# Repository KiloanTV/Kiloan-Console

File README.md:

<div>
  <h1 align="center">Kiloan Desk</h1>

  .png)

  <p align="center">
  <a href="https://blueprint.hackclub.com/">
    </img>
  </a>
  </p>
  <h1></h1>
  <p align="center">
    A customizable mixing console like high quality chassis system for building your own console systems.
  </p>
</div>

<sub align="center">This work is licensed under the
[MIT License](https://mit-license.org).
</sub>

## Table of Contents

- [About](#about)
- [Pictures](#pictures)
- [Bill of Materials](#bill-of-materials)

# About

I have a dream: a self-designed system where everyone can build the perfect mixing console/video console/DIY whatever console out of Aluminum Sheet Metal and a bit of the best hoppyist in house fabrication, 3d printing! And that's why I did this project, it's adapted somewhat to my current wishes and needs, but it can be individually adapted and replicated by anyone without breaking the budget.

# Pictures

# Bill of Materials

<details>
<summary><strong>Show Bill Of Materials(BOM) ----></strong></summary>

|Part Name                                                       |Quantity                                    |Price            |Vendor                                                 |Shipping Cost                                    |Total Cost       |Link(if applicable)                                                                                                                                                                                                                                                             |
|----------------------------------------------------------------|--------------------------------------------|-----------------|-------------------------------------------------------|-------------------------------------------------|-----------------|--------------------------------------------------------------------------------------------------------------------------------------------------------------------------------------------------------------------------------------------------------------------------------|
|Misc Front Module PCBs + Stencil                                |1x5                                         |€9.35            |jlcpcb                                                 |                                                 |                 |                                                                                                                                                                                                                                                                                |
|Fader Front Module PCBs + Stencil                               |1x5                                         |€16.58           |jlcpcb                                                 |                                                 |                 |                                                                                                                                                                                                                                                                                |
|Deck Switcher Front Module PCBs + Stencil                       |1x5                                         |€10.71           |jlcpcb                                                 |Shipping for all 3 PCB orders: €47.18            |                 |                                                                                                                                                                                                                                                                                |
|LCSC Electronic Components for 1x Deck Switcher/2x Fader/2x Misc|1 Order for everything(see lcsc cart export)|€87,81           |lcsc                                                   |€9,37                                            |                 |                                                                                                                                                                                                                                                                                |
|Keyswitches for the PCBs                                        |3x10pcs                                     |€5,20            |aliexpress                                             |€0                                               |                 |https://de.aliexpress.com/item/1005006814061416.html?spm=a2g0o.cart.0.0.639b4ae4hJRiNj&mp=1&pdp_npi=5%40dis%21EUR%21EUR%201.75%21EUR%201.75%21%21EUR%201.75%21%21%21%4021038da617652205559805350e63e4%2112000038390782462%21ct%21DE%216411673618%21%213%210&gatewayAdapt=glo2deu|
|M5x10mm Screws                                                  |3x100pcs                                    |€7,08            |schraubenking-shop.de(local and cheapest in my country)|                                                 |                 |https://www.schraubenking-shop.de/M5-x-10mm-Linsenkopfschrauben-TX-ISO14583-Edelstahl-A2-P004399                                                                                                                                                                                |
|M3x10mm Screws                                                  |1x100pcs                                    |€1,98            |schraubenking-shop.de(local and cheapest in my country)|Shipping for everything from schraubenking: €5,84|                 |https://www.schraubenking-shop.de/M3-x-10mm-Linsenkopfschrauben-TX-ISO14583-Edelstahl-A2-P004381                                                                                                                                                                                |
|JLCCNC Sheet Metal Parts                                        |10 individual parts                         |€146.97          |jlccnc                                                 |€78.28                                           |                 |jlccnc.com                                                                                                                                                                                                                                                                      |
|Estimated Total                                                 |                                            |€285,68 ($335,30)|                                                       |€140.67 ($165,15)                                |€426,35 ($500,56)|                                                                                                                                                                                                                                                                                |

</details>

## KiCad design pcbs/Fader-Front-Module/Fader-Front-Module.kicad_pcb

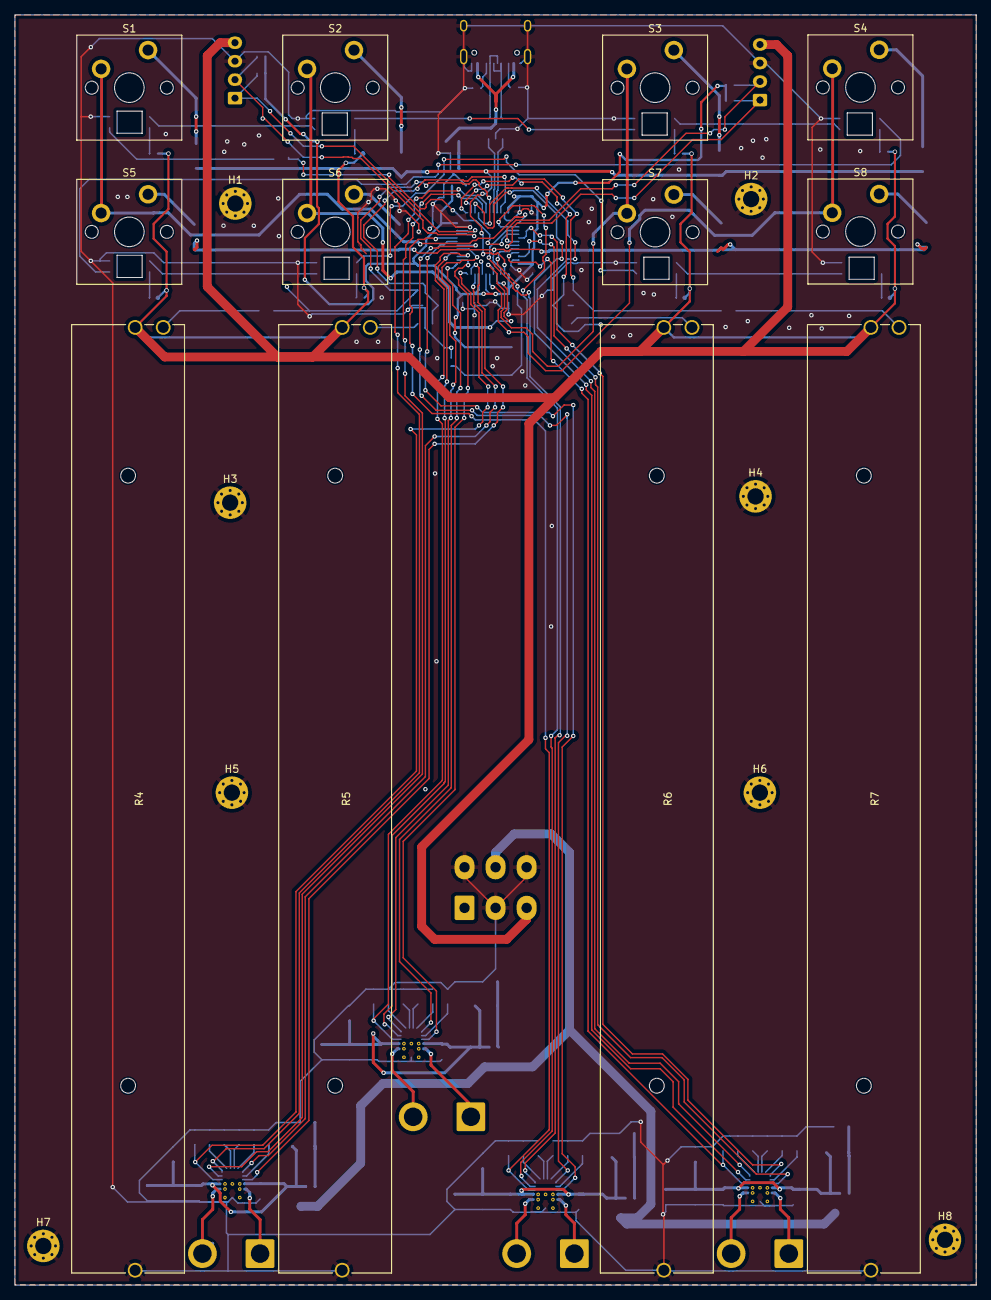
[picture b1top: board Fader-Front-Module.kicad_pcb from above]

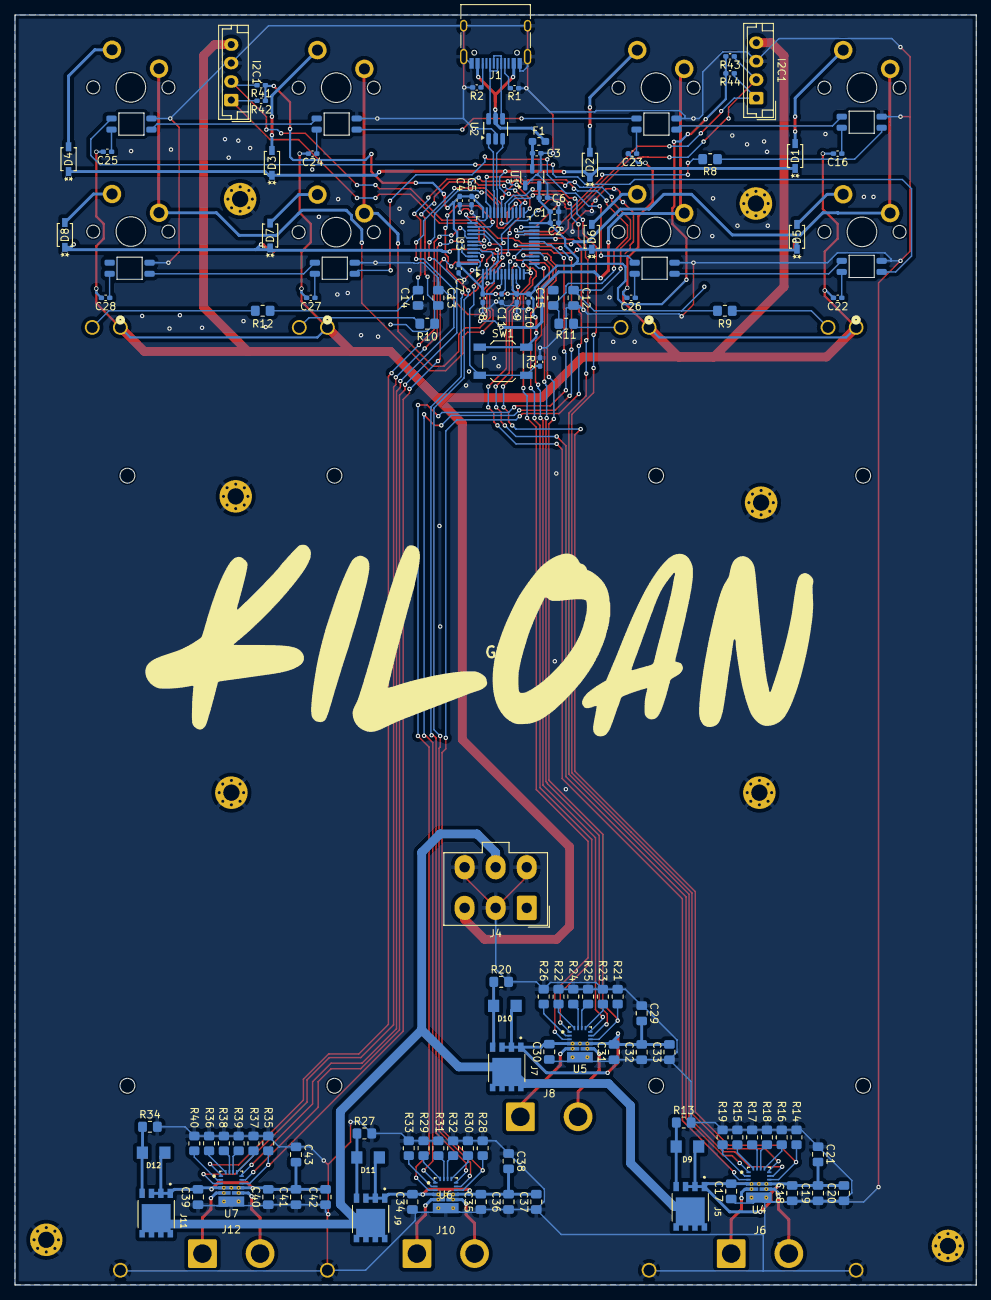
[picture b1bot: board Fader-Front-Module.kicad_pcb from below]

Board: 2 copper layers, 130.0 x 171.8 mm, 144 parts (124 on the bottom side), 113 nets.

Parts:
C1, C2, C5, C9, C11, C16, C22, C23, C24, C25, C26, C27, C28: 100nF; C_0402_1005Metric_Pad0.74x0.62mm_HandSolder
C3, C4, C8: 1uF; C_0402_1005Metric_Pad0.74x0.62mm_HandSolder
C6, C10: 4.7uF; C_0402_1005Metric_Pad0.74x0.62mm_HandSolder
C7: 10nF; C_0402_1005Metric_Pad0.74x0.62mm_HandSolder
C12, C13, C14, C15: 1nF; C_0805_2012Metric_Pad1.18x1.45mm_HandSolder
C17, C21, C29, C30, C34, C35, C39, C40: 10uF; C_0805_2012Metric_Pad1.18x1.45mm_HandSolder
C18, C31, C36, C41: 1uF; C_0805_2012Metric_Pad1.18x1.45mm_HandSolder
C19, C32, C37, C42: 100nF; C_0805_2012Metric_Pad1.18x1.45mm_HandSolder
C20, C33, C38, C43: 10nF; C_0805_2012Metric_Pad1.18x1.45mm_HandSolder
D1, D2, D3, D4, D5, D6, D7, D8: Diode; SOD-123_ONS
D9, D10, D11, D12: Motor Diode; LL-34
F1: 500mA; Fuse_0603_1608Metric_Pad1.05x0.95mm_HandSolder
H1, H2, H3, H4, H5, H6, H7, H8: MountingHole_Pad; MountingHole_2.2mm_M2_Pad_Via
J1: USB_C; USB_C_Receptacle_HRO_TYPE-C-31-M-12
J2, J3: I2C1; JST_EH_B4B-EH-A_1x04_P2.50mm_Vertical
J4: External PowerSupply; Molex_Mini-Fit_Jr_5566-06A_2x03_P4.20mm_Vertical
J5, J7, J9, J11: MOSFET P-CH 40V 70A PDFN5x6-8L; TRANS_TSM018NB03CR_RLG
J6, J8, J10, J12: motor_port_1; SolderWire-2sqmm_1x02_P7.8mm_D2mm_OD3.9mm
LED1, LED2, LED3, LED4, LED5, LED6, LED7, LED8: LED_SK6812MINI
R1, R2, R41, R42, R43, R44: 5.1k; C_0402_1005Metric_Pad0.74x0.62mm_HandSolder
R3: 10k; C_0402_1005Metric_Pad0.74x0.62mm_HandSolder
R4, R5, R6, R7: PTB0153-2010BPB103; schieberegler-PTB0153-2010BPB103
R8, R9, R10, R11, R12: 500Ω; R_0805_2012Metric_Pad1.20x1.40mm_HandSolder
R13, R18, R20, R25, R27, R32, R34, R39: 22kΩ; R_0805_2012Metric_Pad1.20x1.40mm_HandSolder
R14, R21, R28, R35: 1kΩ; R_0805_2012Metric_Pad1.20x1.40mm_HandSolder
R15, R16, R17, R19, R22, R23, R24, R26, R29, R30, R31, R33, R36, R37, R38, R40: 0Ω; R_0805_2012Metric_Pad1.20x1.40mm_HandSolder
S1, S2, S3, S4, S5, S6, S7, S8: Keyswitch; MX_PCB_1.00u
SW1: SW_Push; SW_SPST_TL3342
U1: XC6206; SOT-23-3
U2: USBLC6-2SC6; SOT-23-6_Handsoldering
U3: STM32F072CBT6; LQFP-48_7x7mm_P0.5mm
U4, U5, U6, U7: DRV8243HQRXYRQ1; RXY0014A-MFG

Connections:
+3.3V: C1.2, C2.2, C4.1, C5.2, C6.2, C7.2, C8.2, C9.2, C10.2, R41.2, R42.2, R43.2, R44.2, SW1.1, U1.2 (VO), U3.1 (VBAT), U3.9 (VDDA), U3.24 (VDD), U3.36 (VDDIO2), U3.48 (VDD)
+3.3VA: C16.2, C22.2, C23.2, C24.2, C25.2, C26.2, C27.2, C28.2, J2.4, J3.4, J4.3, R4.1, R5.1, R6.1, R7.1
+5V: C3.1, F1.1, U1.3 (VI)
+5VA: J4.5, J5.5_8 (Pin_9), J7.5_8 (Pin_8), J9.5_8 (Pin_5), J11.5_8 (Pin_9)
/BOOT: R3.2, SW1.2, U3.44 (BOOT0)
/MCU_D+: U2.1 (I/O1), U3.33 (PA12)
/MCU_D-: U2.3 (I/O2), U3.32 (PA11)
/NRST: C11.1, U3.7 (NRST)
/USB_D+: J1.A6 (D+), J1.B6 (D+), U2.6 (I/O1)
/USB_D-: J1.A7 (D-), J1.B7 (D-), U2.4 (I/O2)
Column 0: S1.1, S5.1, U3.37 (PA14)
Column 1: S2.1, S6.1, U3.4 (PC15)
Column 2: S3.1, S7.1, U3.5 (PF0)
Column 3: S4.1, S8.1, U3.6 (PF1)
DIAG_1: R16.1, U4.11 (SCS_N)
DIAG_2: R23.1, U5.11 (SCS_N)
DIAG_3: R30.1, U6.11 (SCS_N)
DIAG_4: R37.1, U7.11 (SCS_N)
DRVOFF_1: R14.1, U3.12 (PA2), U4.8 (DRVOFF)
DRVOFF_2: R21.1, U3.15 (PA5), U5.8 (DRVOFF)
DRVOFF_3: R28.1, U3.20 (PB2), U6.8 (DRVOFF)
DRVOFF_4: R35.1, U3.45 (PB8), U7.8 (DRVOFF)
EN/IN1_1: U3.29 (PA8), U4.9 (EN_IN1)
EN/IN1_2: U3.16 (PA6), U5.9 (EN_IN1)
EN/IN1_3: U3.38 (PA15), U6.9 (EN_IN1)
EN/IN1_4: U3.27 (PB14), U7.9 (EN_IN1)
EN/IN2_1: U3.30 (PA9), U4.10 (PH_IN2)
EN/IN2_2: U3.17 (PA7), U5.10 (PH_IN2)
EN/IN2_3: U3.39 (PB3), U6.10 (PH_IN2)
EN/IN2_4: U3.28 (PB15), U7.10 (PH_IN2)
Fader0: C12.2, R9.1, U3.31 (PA10)
Fader1: C15.2, R11.1, U3.34 (PA13)
Fader2: C13.2, R10.1, U3.25 (PB12)
Fader3: C14.2, R12.1, U3.26 (PB13)
GND: C1.1, C2.1, C3.2, C4.2, C5.1, C6.1, C7.1, C8.1, C9.1, C10.1, C11.2, C12.1, C13.1, C14.1, C15.1, C17.1, C18.1, C19.1, C20.1, C21.1, C29.1, C30.1, C31.1, C32.1, C33.1, C34.1, C35.1, C36.1, C37.1, C38.1, C39.1, C40.1, C41.1, C42.1, C43.1, H1.1, H2.1, H3.1, H4.1, H5.1, H6.1, H7.1, H8.1, J1.A1 (GND), J1.A12 (GND), J1.B1 (GND), J1.B12 (GND), J1.S1 (SHIELD), J2.3, J3.3, J4.2, J4.4, J4.6, LED1.3 (VSS), LED2.3 (VSS), LED3.3 (VSS), LED4.3 (VSS), LED5.3 (VSS), LED6.3 (VSS), LED7.3 (VSS), LED8.3 (VSS), R1.2, R2.2, R3.1, R4.3, R5.3, R6.3, R7.3, R13.2, R14.2, R15.2, R16.2, R17.2, R18.2, R19.2, R20.2, R21.2, R22.2, R23.2, R24.2, R25.2, R26.2, R27.2, R28.2, R29.2, R30.2, R31.2, R32.2, R33.2, R34.2, R35.2, R36.2, R37.2, R38.2, R39.2, R40.2, U1.1 (GND), U2.2 (GND), U3.8 (VSSA), U3.23 (VSS), U3.35 (VSS), U3.47 (VSS), U4.6 (GND), U5.6 (GND), U6.6 (GND), U7.6 (GND)
I2C1_SCL: J2.2, R41.1, U3.42 (PB6)
I2C1_SDA: J2.1, R42.1, U3.43 (PB7)
I2C2_SCL: J3.2, R43.1, U3.21 (PB10)
I2C2_SDA: J3.1, R44.1, U3.22 (PB11)
IPROPI_1: R19.1, U4.2 (IPROPI)
IPROPI_2: R26.1, U5.2 (IPROPI)
IPROPI_3: R33.1, U6.2 (IPROPI)
IPROPI_4: R40.1, U7.2 (IPROPI)
ITRIP_1: R17.1, U4.13 (SDI)
ITRIP_2: R24.1, U5.13 (SDI)
ITRIP_3: R31.1, U6.13 (SDI)
ITRIP_4: R38.1, U7.13 (SDI)
LED_DATA_IN: R8.2, U3.40 (PB4)
MODE_1: R15.1, U4.14 (SDO)
MODE_2: R22.1, U5.14 (SDO)
MODE_3: R29.1, U6.14 (SDO)
MODE_4: R36.1, U7.14 (SDO)
unnamed: D1.2 (A), S1.2
unnamed: D2.2 (A), S2.2
unnamed: D3.2 (A), S3.2
unnamed: D4.2 (A), S4.2
unnamed: D5.2 (A), S5.2
unnamed: D6.2 (A), S6.2
unnamed: D7.2 (A), S7.2
unnamed: D8.2 (A), S8.2
unnamed: D9.2 (A), J5.4, R13.1
unnamed: D10.2 (A), J7.4, R20.1
unnamed: D11.2 (A), J9.4, R27.1
unnamed: D12.2 (A), J11.4, R34.1
unnamed: J1.A5 (CC1), R1.1
unnamed: J1.B5 (CC2), R2.1
unnamed: LED1.2 (DIN), R8.1
unnamed: LED1.4 (DOUT), LED2.2 (DIN)
unnamed: C16.1, LED1.1 (VDD)
unnamed: LED2.4 (DOUT), LED3.2 (DIN)
unnamed: C23.1, LED2.1 (VDD)
unnamed: LED3.4 (DOUT), LED4.2 (DIN)
unnamed: C24.1, LED3.1 (VDD)
unnamed: LED4.4 (DOUT), LED5.2 (DIN)
unnamed: C25.1, LED4.1 (VDD)
unnamed: LED5.4 (DOUT), LED6.2 (DIN)
unnamed: C22.1, LED5.1 (VDD)
unnamed: LED6.4 (DOUT), LED7.2 (DIN)
unnamed: C26.1, LED6.1 (VDD)
unnamed: LED7.4 (DOUT), LED8.2 (DIN)
unnamed: C27.1, LED7.1 (VDD)
unnamed: C28.1, LED8.1 (VDD)
unnamed: R4.2, R9.2
unnamed: R6.2, R10.2
unnamed: R5.2, R11.2
unnamed: R7.2, R12.2
OUT1_1: J6.2, U4.7 (OUT1)
OUT1_2: J8.2, U5.7 (OUT1)
OUT1_3: J10.2, U6.7 (OUT1)
OUT1_4: J12.2, U7.7 (OUT1)
OUT2_1: J6.1, U4.5 (OUT2)
OUT2_2: J8.1, U5.5 (OUT2)
OUT2_3: J10.1, U6.5 (OUT2)
OUT2_4: J12.1, U7.5 (OUT2)
Row 0: D1.1 (K), D2.1 (K), D3.1 (K), D4.1 (K), U3.2 (PC13)
Row 1: D5.1 (K), D6.1 (K), D7.1 (K), D8.1 (K), U3.3 (PC14)
SR_1: R18.1, U4.12 (SCLK)
SR_2: R25.1, U5.12 (SCLK)
SR_3: R32.1, U6.12 (SCLK)
SR_4: R39.1, U7.12 (SCLK)
VBUS: F1.2, J1.A4 (VBUS), J1.A9 (VBUS), J1.B4 (VBUS), J1.B9 (VBUS), U2.5 (VBUS)
VSS_1: C17.2, C18.2, C19.2, C20.2, C21.2, D9.1 (K), J5.1, J5.2, J5.3, U4.4 (VM)
VSS_2: C29.2, C30.2, C31.2, C32.2, C33.2, D10.1 (K), J7.1, J7.2, J7.3, U5.4 (VM)
VSS_3: C34.2, C35.2, C36.2, C37.2, C38.2, D11.1 (K), J9.1, J9.2, J9.3, U6.4 (VM)
VSS_4: C39.2, C40.2, C41.2, C42.2, C43.2, D12.1 (K), J11.1, J11.2, J11.3, U7.4 (VM)
nFAULT_1: U3.10 (PA0), U4.1 (FAULT_N)
nFAULT_2: U3.13 (PA3), U5.1 (FAULT_N)
nFAULT_3: U3.18 (PB0), U6.1 (FAULT_N)
nFAULT_4: U3.41 (PB5), U7.1 (FAULT_N)
nSLEEP_1: U3.11 (PA1), U4.3 (SLEEP_N)
nSLEEP_2: U3.14 (PA4), U5.3 (SLEEP_N)
nSLEEP_3: U3.19 (PB1), U6.3 (SLEEP_N)
nSLEEP_4: U3.46 (PB9), U7.3 (SLEEP_N)

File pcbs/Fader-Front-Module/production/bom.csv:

Designator,Footprint,Quantity,Value,LCSC Part #
"C1, C11, C16, C2, C22, C23, C24, C25, C26, C27, C28, C5, C9",0402,13,100nF,C307331
"C10, C6",0402,2,4.7uF,C23733
"C12, C13, C14, C15",0805,4,1nF,C94121
"C17, C21, C29, C30, C34, C35, C39, C40",0805,8,10uF,C15850
"C18, C31, C36, C41",0805,4,1uF,C28323
"C19, C32, C37, C42",0805,4,100nF,C49678
"C20, C33, C38, C43",0805,4,10nF,C1710
"C3, C4, C8",0402,3,1uF,C52923
C7,0402,1,10nF,C15195
"D1, D2, D3, D4, D5, D6, D7, D8",SOD-123_ONS,8,Diode,C11177
"D10, D11, D12, D9",LL-34,4,Motor Diode,C2891753
F1,0603,1,500mA,C210357
J1,USB_C_Receptacle_HRO_TYPE-C-31-M-12,1,USB_C,C165948
"J10, J12, J6, J8",SolderWire-2sqmm_1x02_P7.8mm_D2mm_OD3.9mm,4,motor_port_1,
"J11, J5, J7, J9",TRANS_TSM018NB03CR_RLG,4,MOSFET P-CH 40V 70A PDFN5x6-8L,C5297498
"J2, J3",JST_EH_B4B-EH-A_1x04_P2.50mm_Vertical,2,I2C1,C160258
J4,Molex_Mini-Fit_Jr_5566-06A_2x03_P4.20mm_Vertical,1,External PowerSupply,C471417
"LED1, LED2, LED3, LED4, LED5, LED6, LED7, LED8",LED_SK6812MINI,8,LED_SK6812MINI,C5149201
"R1, R2, R41, R42, R43, R44",0402,6,5.1k,C25905
"R10, R11, R12, R8, R9",0805,5,500Ω,C2828857
"R13, R18, R20, R25, R27, R32, R34, R39",0805,8,22kΩ,C2907243
"R14, R21, R28, R35",0805,4,1kΩ,C95781
"R15, R16, R17, R19, R22, R23, R24, R26, R29, R30, R31, R33, R36, R37, R38, R40",0805,16,0Ω,DNP
R3,0402,1,10k,C25744
"R4, R5, R6, R7",schieberegler-PTB0153-2010BPB103,4,PTB0153-2010BPB103,C17427549
"S1, S2, S3, S4, S5, S6, S7, S8",MX_PCB_1.00u,8,Keyswitch,
SW1,SW_SPST_TL3342,1,SW_Push,C115351
U1,SOT-23-3,1,XC6206,C5446
U2,SOT-23-6_Handsoldering,1,USBLC6-2SC6,C2827654
U3,LQFP-48_7x7mm_P0.5mm,1,STM32F072CBT6,C81720
"U4, U5, U6, U7",RXY0014A-MFG,4,DRV8243HQRXYRQ1,C3040833

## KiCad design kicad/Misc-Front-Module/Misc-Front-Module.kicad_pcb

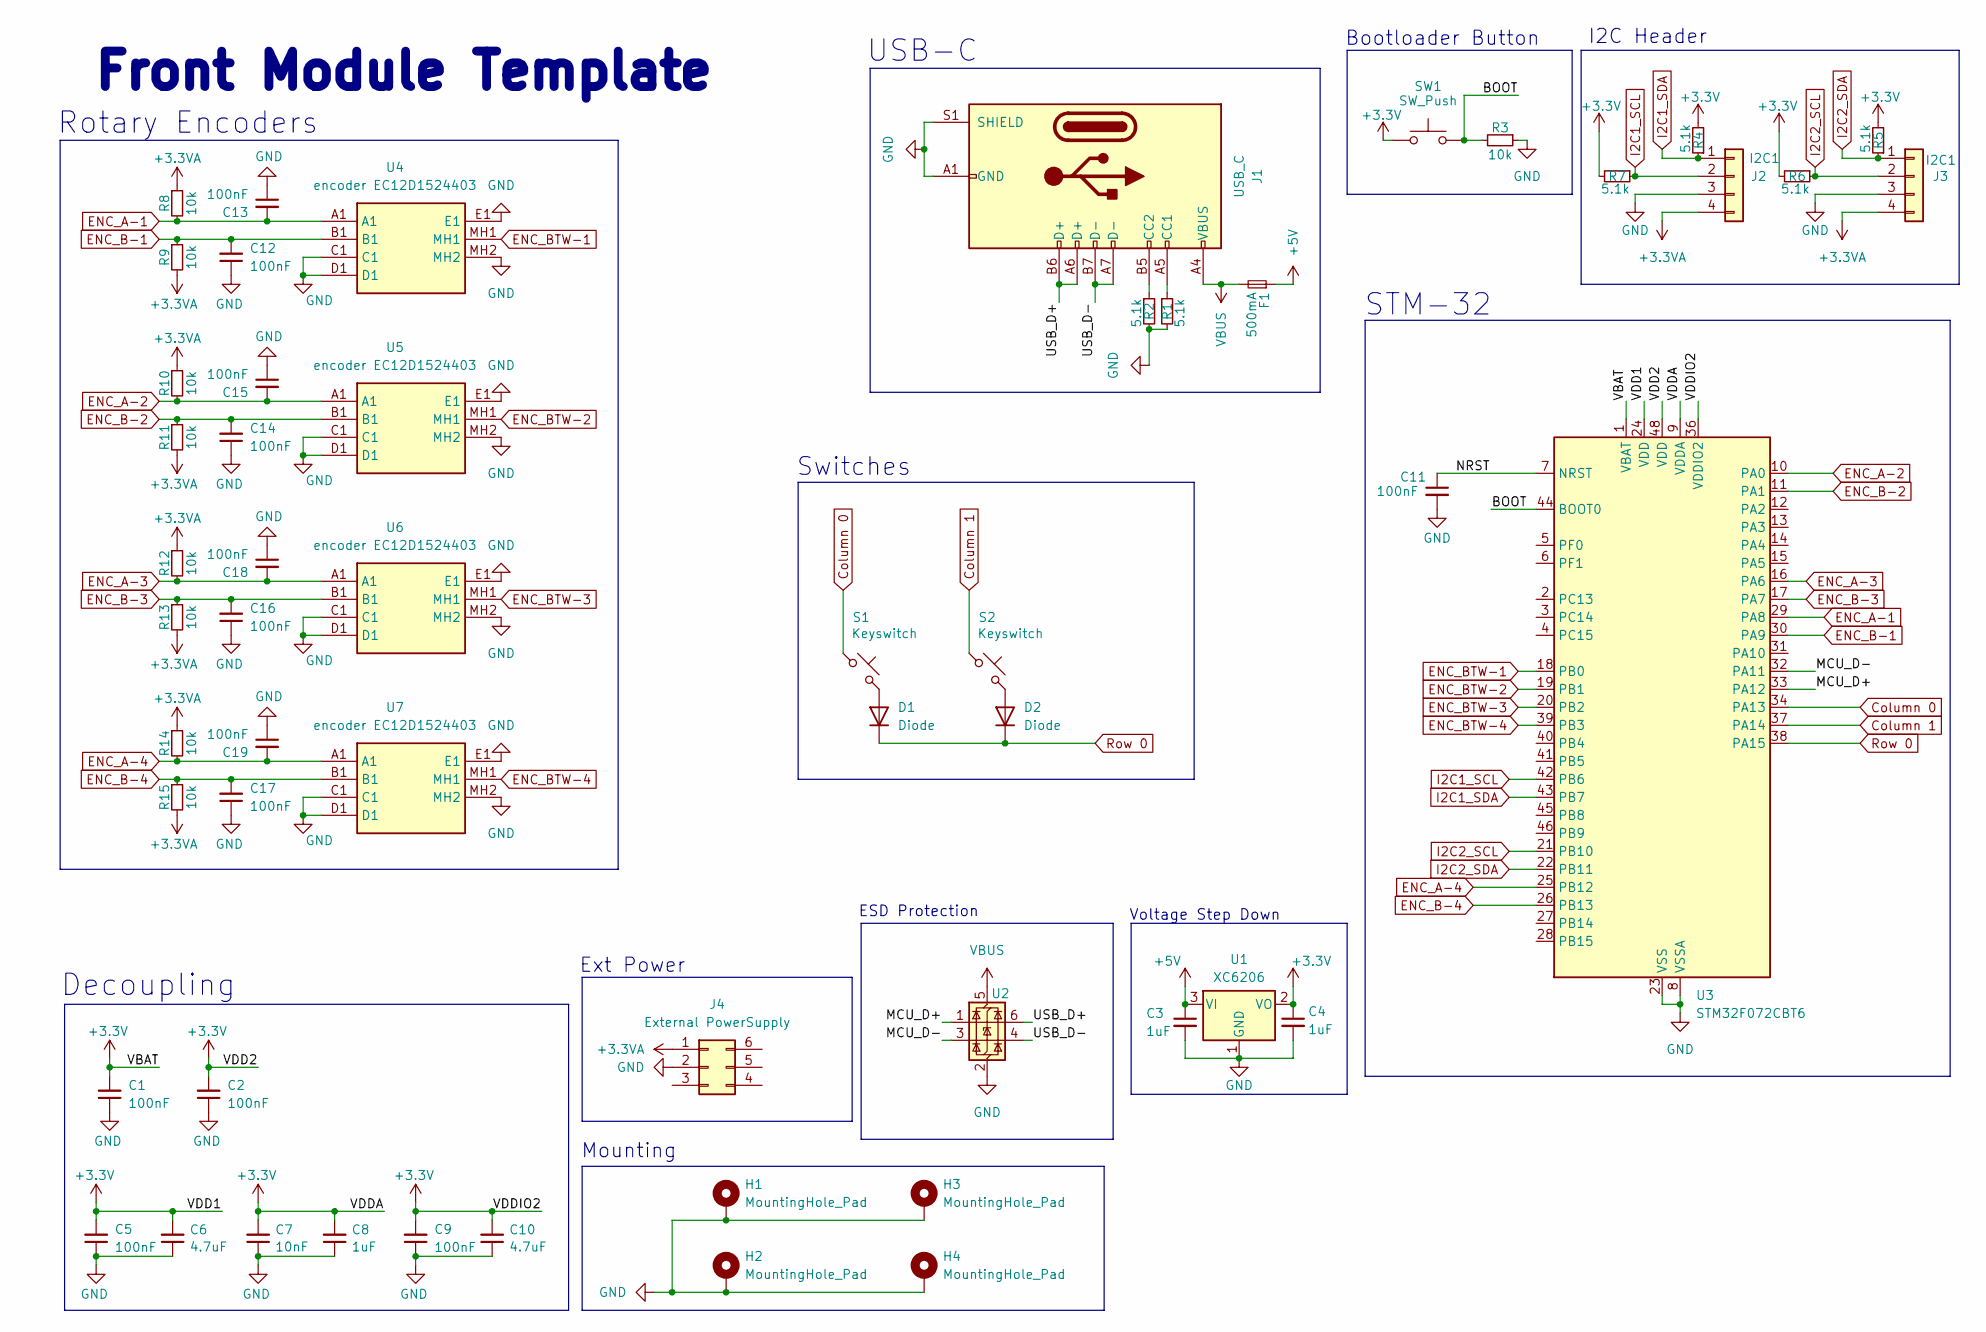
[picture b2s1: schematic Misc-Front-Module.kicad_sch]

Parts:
C1, C11: 100nF; C_0402_1005Metric_Pad0.74x0.62mm_HandSolder; LCSC C307331
C2, C5, C9, C12, C13, C14, C15, C16, C17, C18, C19: 100nF; C_0402_1005Metric_Pad0.74x0.62mm_HandSolder; MPN CL05B104KB54PNC; LCSC C307331
C3, C4: 1uF; C_0402_1005Metric_Pad0.74x0.62mm_HandSolder; LCSC C52923
C6, C10: 4.7uF; C_0402_1005Metric_Pad0.74x0.62mm_HandSolder; MPN CL05A475MP5NRNC; LCSC C23733
C7: 10nF; C_0402_1005Metric_Pad0.74x0.62mm_HandSolder; MPN CL05B103KB5NNNC; LCSC C15195
C8: 1uF; C_0402_1005Metric_Pad0.74x0.62mm_HandSolder; MPN CL05A105KA5NQNC; LCSC C52923
D1, D2: Diode; SOD-123_ONS; LCSC C11177
F1: 500mA; Fuse_0603_1608Metric_Pad1.05x0.95mm_HandSolder; LCSC C210357
H1, H2, H3, H4: MountingHole_Pad; MountingHole_2.2mm_M2_Pad_Via
J1: USB_C; USB_C_Receptacle_HRO_TYPE-C-31-M-12; LCSC C165948
J2, J3: I2C1; JST_EH_B4B-EH-A_1x04_P2.50mm_Vertical; LCSC C160258
J4: External PowerSupply; SolderWire-2sqmm_1x02_P7.8mm_D2mm_OD3.9mm; LCSC C471417
R1, R2, R4, R5, R6, R7: 5.1k; C_0402_1005Metric_Pad0.74x0.62mm_HandSolder; LCSC C25905
R3, R8, R9, R10, R11, R12, R13, R14, R15: 10k; C_0402_1005Metric_Pad0.74x0.62mm_HandSolder; LCSC C25744
S1, S2: Keyswitch; MX_PCB_1.00u
SW1: SW_Push; SW_SPST_TL3342; LCSC C115351
U1: XC6206; SOT-23-3; LCSC C5446
U2: USBLC6-2SC6; SOT-23-6_Handsoldering; LCSC C2827654
U3: STM32F072CBT6; LQFP-48_7x7mm_P0.5mm; LCSC C81720
U4, U5, U6, U7: encoder EC12D1524403; EC12D1524403; LCSC C112349

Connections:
+3.3V: C1.2, C2.2, C4.1, C5.2, C6.2, C7.2, C8.2, C9.2, C10.2, R4.2, R5.2, R6.2, R7.2, SW1.1, U1.2 (VO), U3.1 (VBAT), U3.9 (VDDA), U3.24 (VDD), U3.36 (VDDIO2), U3.48 (VDD)
+3.3VA: J2.4, J3.4, J4.1, R8.1, R9.2, R10.1, R11.2, R12.1, R13.2, R14.1, R15.2
+5V: C3.1, F1.1, U1.3 (VI)
/BOOT: R3.2, SW1.2, U3.44 (BOOT0)
/MCU_D+: U2.1 (I/O1), U3.33 (PA12)
/MCU_D-: U2.3 (I/O2), U3.32 (PA11)
/NRST: C11.1, U3.7 (NRST)
/USB_D+: J1.A6 (D+), J1.B6 (D+), U2.6 (I/O1)
/USB_D-: J1.A7 (D-), J1.B7 (D-), U2.4 (I/O2)
Column 0: S1.1, U3.34 (PA13)
Column 1: S2.1, U3.37 (PA14)
ENC_A-1: C13.2, R8.2, U3.29 (PA8), U4.A1
ENC_A-2: C15.2, R10.2, U3.10 (PA0), U5.A1
ENC_A-3: C18.2, R12.2, U3.16 (PA6), U6.A1
ENC_A-4: C19.2, R14.2, U3.25 (PB12), U7.A1
ENC_B-1: C12.2, R9.1, U3.30 (PA9), U4.B1
ENC_B-2: C14.2, R11.1, U3.11 (PA1), U5.B1
ENC_B-3: C16.2, R13.1, U3.17 (PA7), U6.B1
ENC_B-4: C17.2, R15.1, U3.26 (PB13), U7.B1
ENC_BTW-1: U3.18 (PB0), U4.MH1
ENC_BTW-2: U3.19 (PB1), U5.MH1
ENC_BTW-3: U3.20 (PB2), U6.MH1
ENC_BTW-4: U3.39 (PB3), U7.MH1
GND: C1.1, C2.1, C3.2, C4.2, C5.1, C6.1, C7.1, C8.1, C9.1, C10.1, C11.2, C12.1, C13.1, C14.1, C15.1, C16.1, C17.1, C18.1, C19.1, H1.1, H2.1, H3.1, H4.1, J1.A1 (GND), J1.A12 (GND), J1.B1 (GND), J1.B12 (GND), J1.S1 (SHIELD), J2.3, J3.3, J4.2, R1.2, R2.2, R3.1, U1.1 (GND), U2.2 (GND), U3.8 (VSSA), U3.23 (VSS), U3.35 (VSS), U3.47 (VSS), U4.C1, U4.D1, U4.E1, U4.MH2, U5.C1, U5.D1, U5.E1, U5.MH2, U6.C1, U6.D1, U6.E1, U6.MH2, U7.C1, U7.D1, U7.E1, U7.MH2
I2C1_SCL: J2.2, R7.1, U3.42 (PB6)
I2C1_SDA: J2.1, R4.1, U3.43 (PB7)
I2C2_SCL: J3.2, R6.1, U3.21 (PB10)
I2C2_SDA: J3.1, R5.1, U3.22 (PB11)
unnamed: D1.2 (A), S1.2
unnamed: D2.2 (A), S2.2
unnamed: J1.A5 (CC1), R1.1
unnamed: J1.B5 (CC2), R2.1
Row 0: D1.1 (K), D2.1 (K), U3.38 (PA15)
VBUS: F1.2, J1.A4 (VBUS), J1.A9 (VBUS), J1.B4 (VBUS), J1.B9 (VBUS), U2.5 (VBUS)

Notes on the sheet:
ESD Protection
I2C Header
Mounting
Ext Power
Voltage Step Down
Bootloader Button
Switches
Decoupling
STM-32
USB-C
Front Module Template
Rotary Encoders

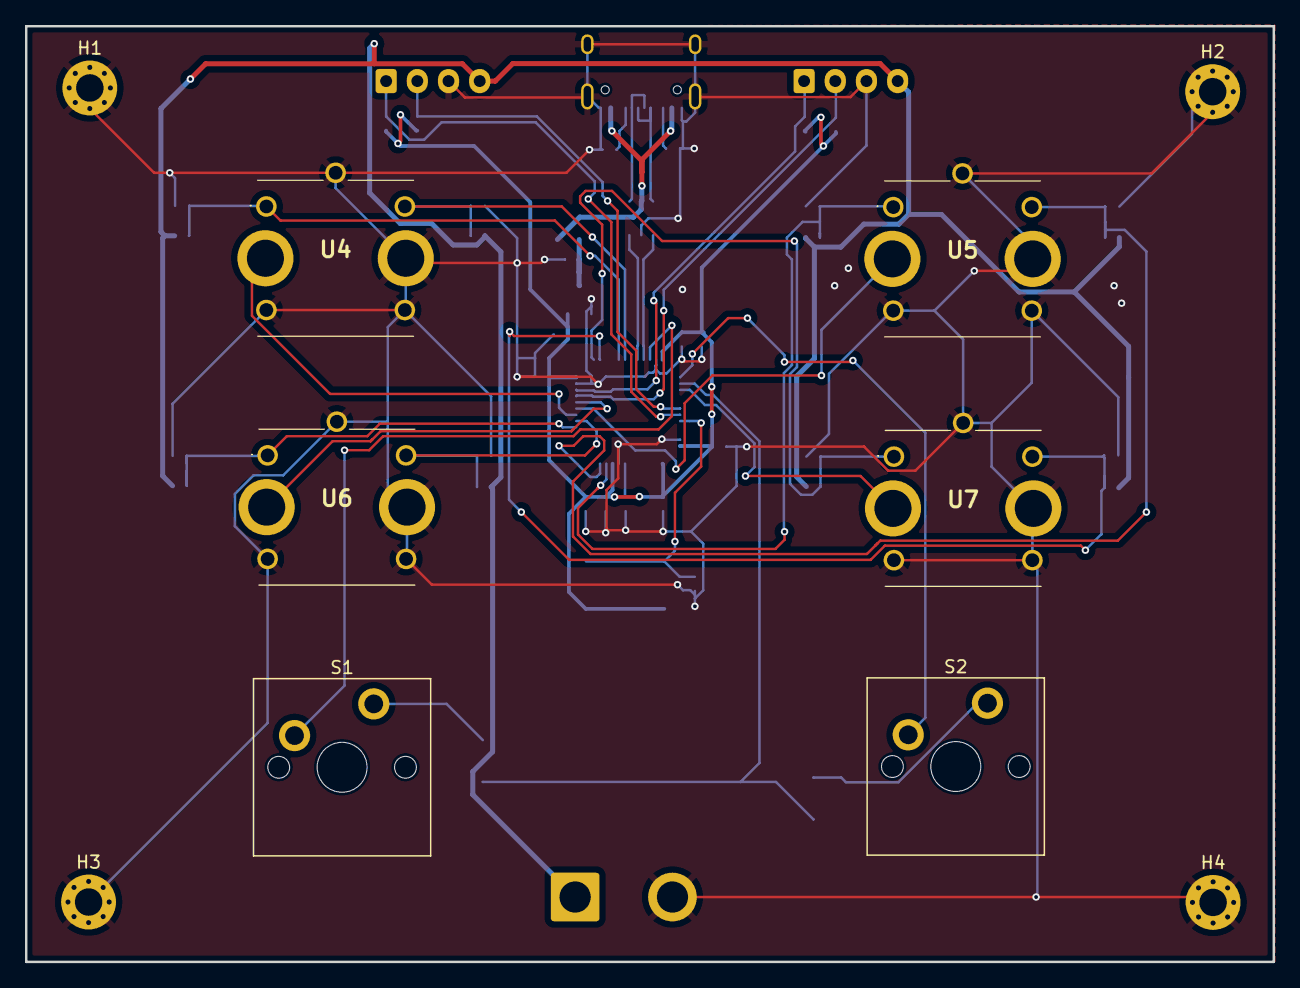
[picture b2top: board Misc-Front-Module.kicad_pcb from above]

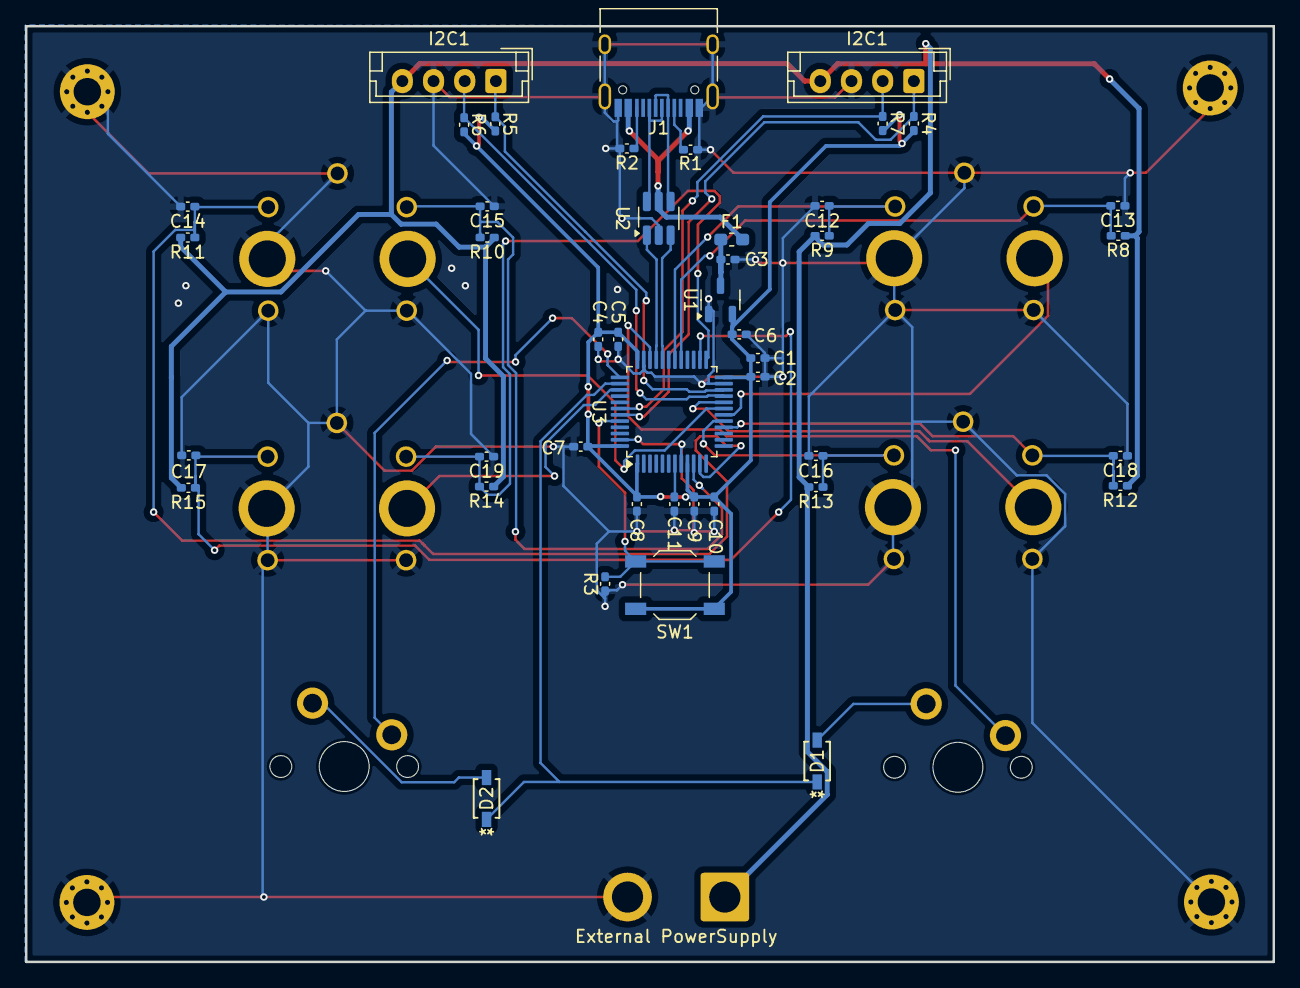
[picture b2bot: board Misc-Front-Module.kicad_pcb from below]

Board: 2 copper layers, 100.0 x 75.0 mm, 55 parts (44 on the bottom side), 34 nets.

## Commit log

2025-12-03 Add files
    _ Kian
2025-12-08 modfiy left/right panel + add baseplate
    _ Kian
2025-12-10 add bom
    _ Kian
2025-12-12 add estimated total and quote from jlccnc
2025-12-13 made bom easier to understand
    _ Kian
